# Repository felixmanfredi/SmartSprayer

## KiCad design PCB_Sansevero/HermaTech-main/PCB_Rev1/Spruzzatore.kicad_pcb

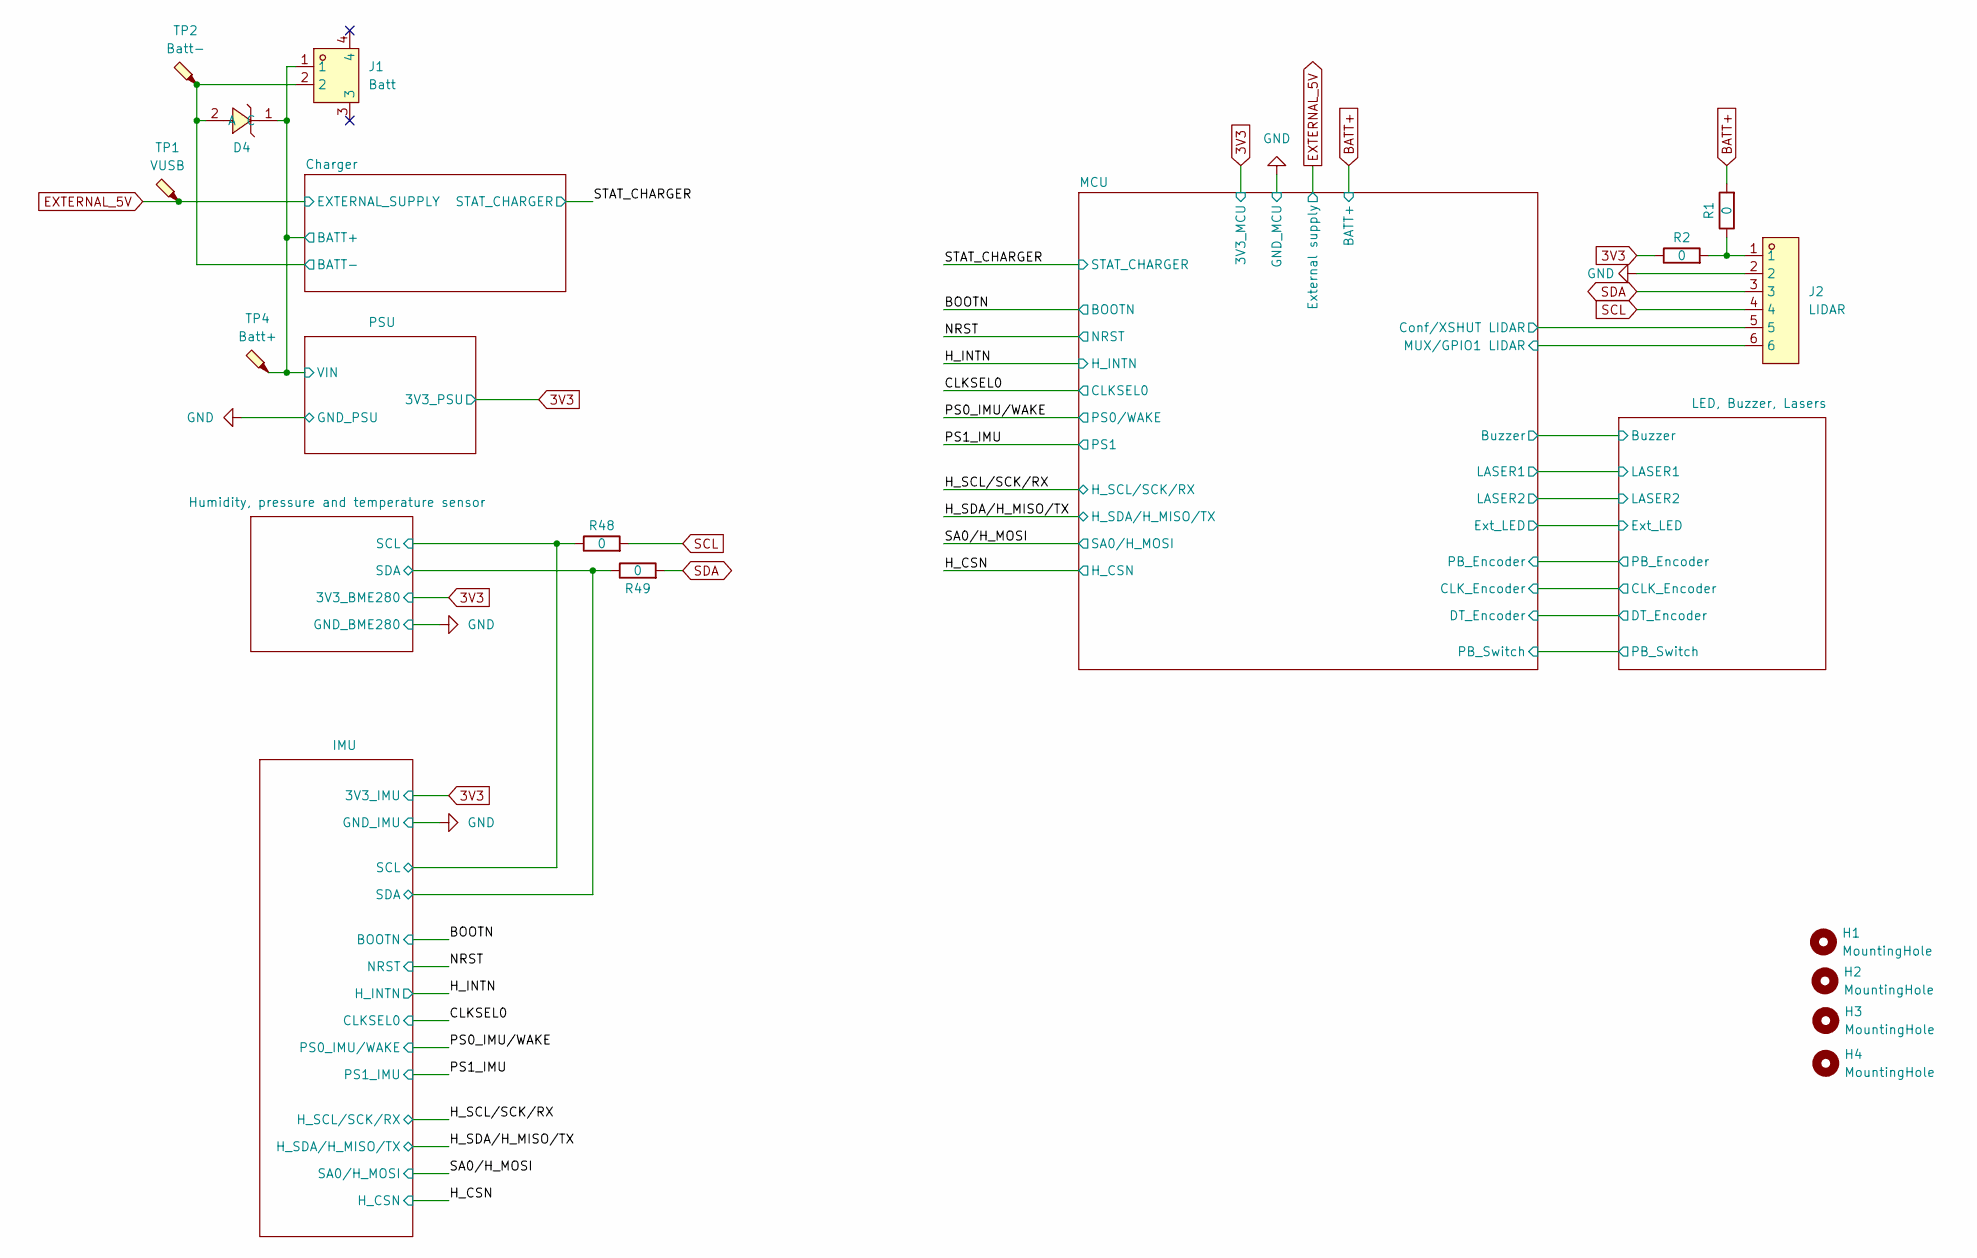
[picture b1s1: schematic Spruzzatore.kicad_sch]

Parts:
D4: SLESD4V5S; SOD-323_L1.7-W1.3-LS2.6-RD-1; LCSC Part C5155454
H1, H2, H3, H4: MountingHole; MountingHole_3.2mm_M3_DIN965_Pad
J1: Batt; CONN-SMD_P2.00_S2B-PH-SM4-TB-LF-SN; LCSC Part C295747
J2: LIDAR; CONN-TH_6P-P1.25_BX-MX1.25-6PZZ; LCSC Part C22388452
R1, R2, R48, R49: 0; R0603; LCSC Part C21189
TP1: VUSB; TestPoint_Pad_D1.0mm
TP2: Batt-; TestPoint_Pad_1.0x1.0mm
TP4: Batt+; TestPoint_Pad_D1.0mm

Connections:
3V3: R2.1; also elsewhere on the board
/Charger/BATT-: D4.2 (A), J1.2, TP2.1; also elsewhere on the board
/Charger/B_CHG_+: D4.1 (C), J1.1, TP4.1; also elsewhere on the board
/Humidity, pressure and temperature sensor/SCL: R48.1; also elsewhere on the board
/Humidity, pressure and temperature sensor/SDA: R49.1; also elsewhere on the board
/MCU/Conf/XSHUT LIDAR: J2.5; also elsewhere on the board
/MCU/MUX/GPIO1 LIDAR: J2.6; also elsewhere on the board
BATT+: R1.2; also elsewhere on the board
EXTERNAL_5V: TP1.1; also elsewhere on the board
GND: J2.2; also elsewhere on the board
unnamed: J2.1, R1.1, R2.2
SCL: J2.4, R48.2; also elsewhere on the board
SDA: J2.3, R49.2; also elsewhere on the board

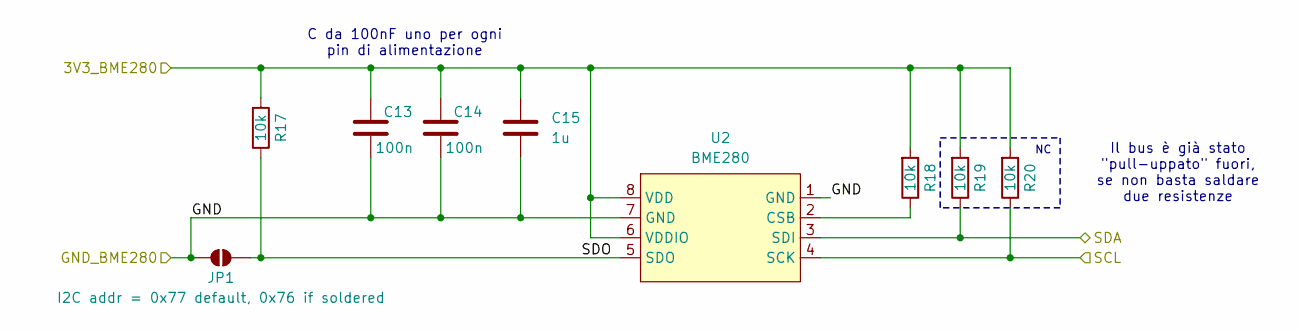
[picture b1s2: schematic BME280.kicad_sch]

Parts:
C13, C14: 100n; C0603; LCSC Part C14663
C15: 1u; C0603; LCSC Part C15849
JP1: I2C addr = 0x77 default, 0x76 if soldered; SolderJumper-2_P1.3mm_Open_RoundedPad1.0x1.5mm
R17, R18, R19, R20: 10k; R0603; LCSC Part C25804
U2: BME280; LGA-8_BME280_BL; LCSC Part C92489

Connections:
3V3: C13.1, C14.1, C15.1, R17.2, R18.2, R19.2, R20.2, U2.6 (VDDIO), U2.8 (VDD); also elsewhere on the board
/Humidity, pressure and temperature sensor/SCL: R20.1, U2.4 (SCK); also elsewhere on the board
/Humidity, pressure and temperature sensor/SDA: R19.1, U2.3 (SDI); also elsewhere on the board
/Humidity, pressure and temperature sensor/SDO: JP1.1 (A), R17.1, U2.5 (SDO)
GND: C13.2, C14.2, C15.2, JP1.2 (B), U2.1 (GND), U2.7 (GND); also elsewhere on the board
unnamed: R18.1, U2.2 (CSB)

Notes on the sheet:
C da 100nF uno per ogni pin di alimentazione
Il bus è già stato "pull-uppato" fuori, se non basta saldare due resistenze

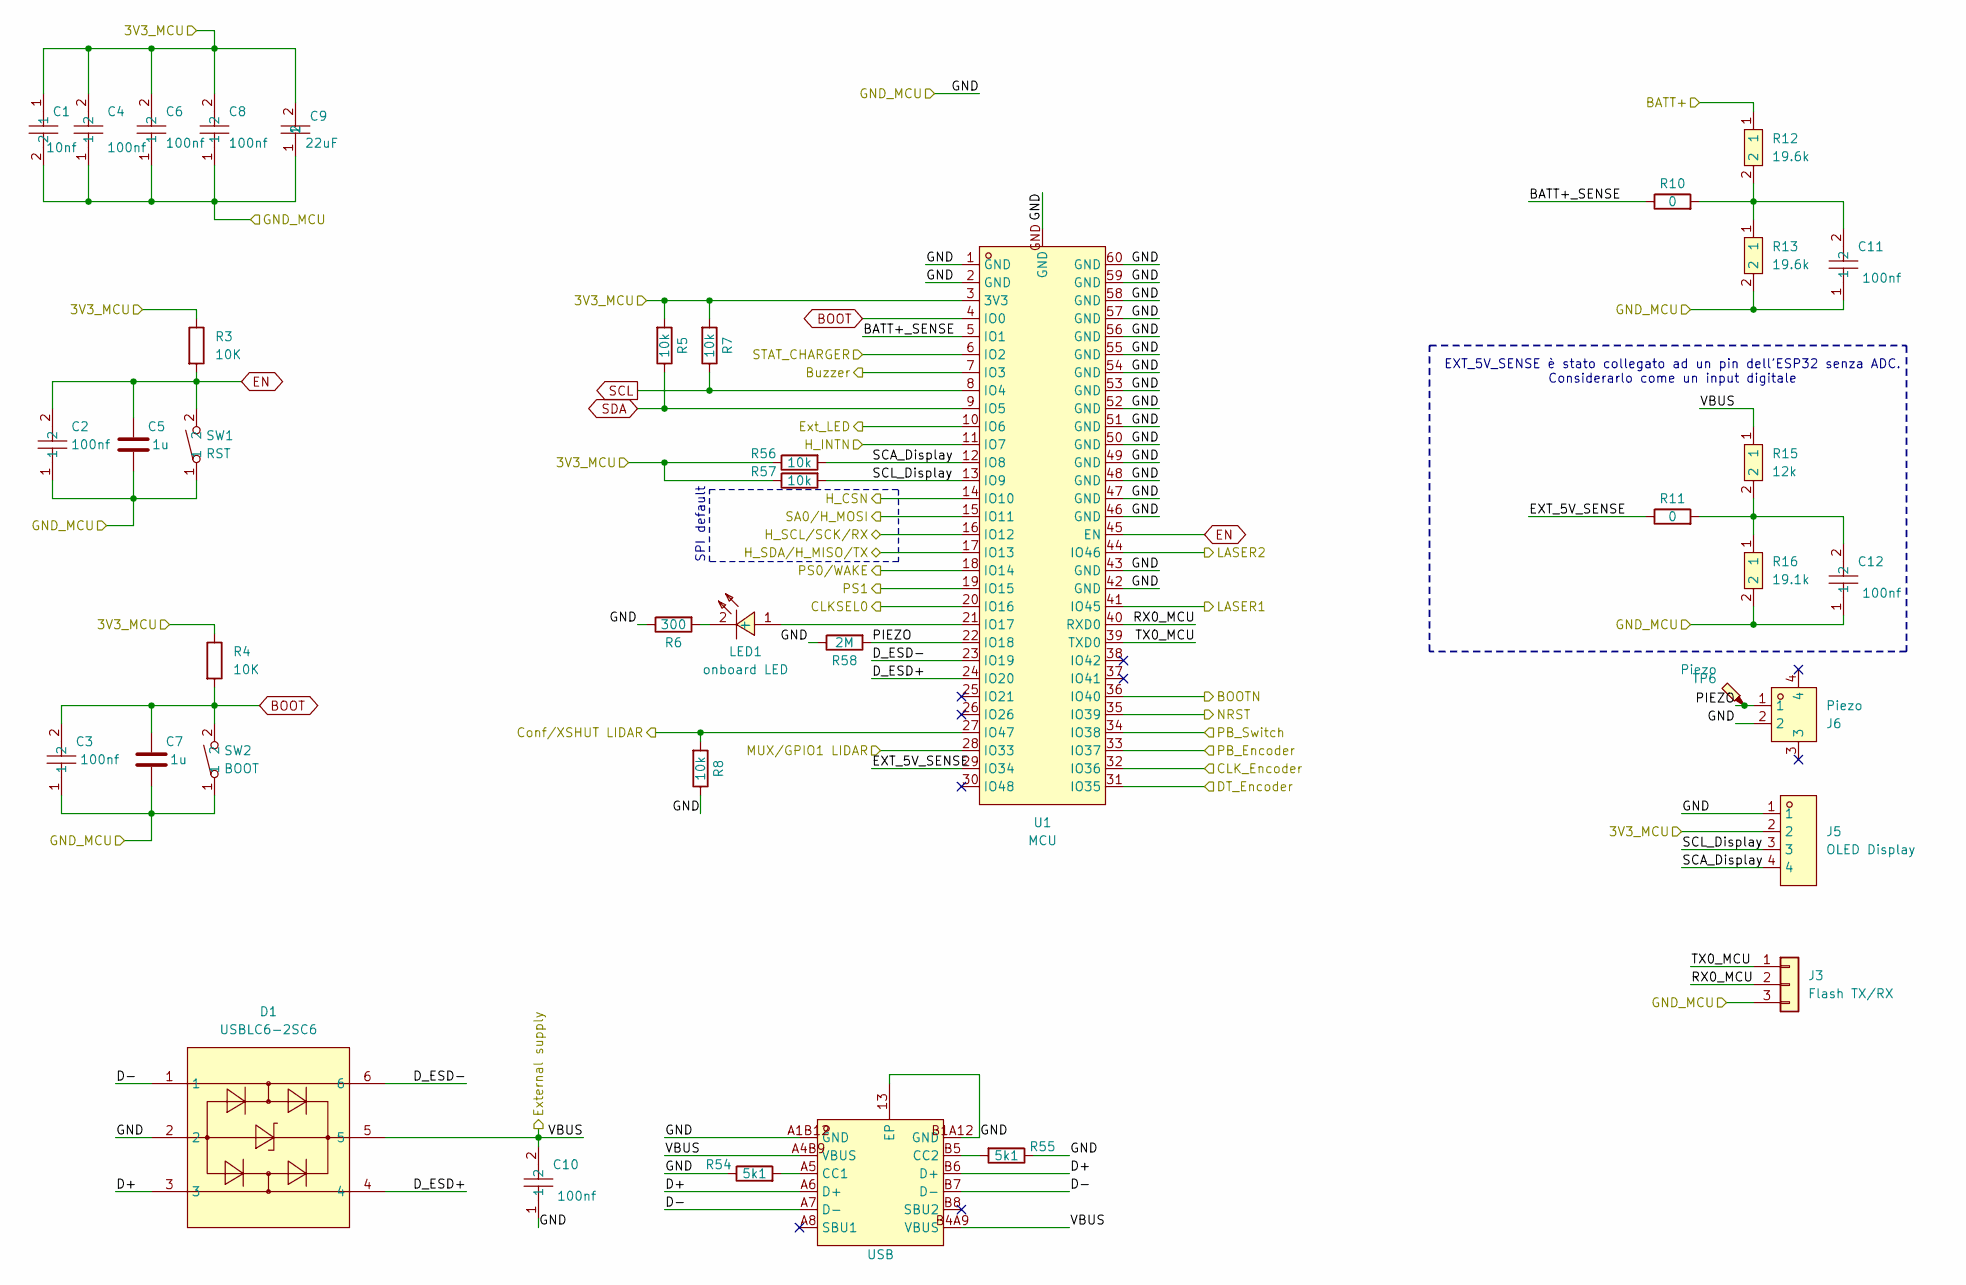
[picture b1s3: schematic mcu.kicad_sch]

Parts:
C1: 10nf; C0603; LCSC Part C57112
C2, C3, C4, C6, C8, C10, C11, C12: 100nf; C0603; LCSC Part C14663
C5, C7: 1u; C0603; LCSC part C15849
C9: 22uF; C1206; LCSC Part C12891
D1: USBLC6-2SC6; SOT-23-6_L2.9-W1.6-P0.95-LS2.8-BL; LCSC Part C2687116
J3: Flash TX/RX; JST_GH_SM03B-GHS-TB_1x03-1MP_P1.25mm_Horizontal
J5: OLED Display; CONN-TH_4P-P1.25_WAFER-MX1.25-4PZZ; LCSC Part C22390409
J6: Piezo; CONN-SMD_2P-P1.25_XUNPU_WAFER-MX1.25-2PWB; LCSC Part C3029359
LED1: onboard LED; LED0805-R-RD; LCSC Part C84256
R3, R4: 10K; R0603; LCSC Part C25804
R5, R7, R56, R57: 10k; R0603; LCSC Part C25804
R6: 300; R0603; LCSC Part C23025
R8: 10k; R0603
R10, R11: 0; R0603; LCSC Part C21189
R12, R13: 19.6k; R0603; LCSC Part C861185
R15: 12k; R0603; LCSC Part C861185
R16: 19.1k; R0603; LCSC Part C861097
R54, R55: 5k1; R0603; LCSC C23186
R58: 2M; R0603; LCSC Part C23025
SW1: RST; SW-SMD_L3.9-W2.9-P4.15-LS5.0; LCSC Part C493285
SW2: BOOT; SW-SMD_L3.9-W2.9-P4.15-LS5.0; LCSC Part C493285
TP6: Piezo; TestPoint_Pad_D1.0mm
U1: MCU; BULETM-SMD_ESP32-S3-MINI-1-N8; LCSC Part C3013941
USB1: USB; USB-C-SMD_TYPE-C-16P-1; LCSC Part C2982555

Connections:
3V3: C1.1, C4.2, C6.2, C8.2, C9.2, J5.2, R3.1, R4.1, R5.2, R7.2, R56.1, R57.1, U1.3 (3V3); also elsewhere on the board
/BOOTN: U1.36 (IO40); also elsewhere on the board
/CLKSEL0: U1.20 (IO16); also elsewhere on the board
/H_CSN: U1.14 (IO10); also elsewhere on the board
/H_INTN: U1.11 (IO7); also elsewhere on the board
/H_SCL/SCK/RX: U1.16 (IO12); also elsewhere on the board
/H_SDA/H_MISO/TX: U1.17 (IO13); also elsewhere on the board
/LED, Buzzer, Lasers/Buzzer: U1.7 (IO3); also elsewhere on the board
/LED, Buzzer, Lasers/CLK_Encoder: U1.32 (IO36); also elsewhere on the board
/LED, Buzzer, Lasers/DT_Encoder: U1.31 (IO35); also elsewhere on the board
/LED, Buzzer, Lasers/Ext_LED: U1.10 (IO6); also elsewhere on the board
/LED, Buzzer, Lasers/LASER1: U1.41 (IO45); also elsewhere on the board
/LED, Buzzer, Lasers/LASER2: U1.44 (IO46); also elsewhere on the board
/LED, Buzzer, Lasers/PB_Encoder: U1.33 (IO37); also elsewhere on the board
/LED, Buzzer, Lasers/PB_Switch: U1.34 (IO38); also elsewhere on the board
/MCU/BATT+_SENSE: R10.1, U1.5 (IO1)
/MCU/Conf/XSHUT LIDAR: R8.2, U1.27 (IO47); also elsewhere on the board
/MCU/D+: D1.3, USB1.A6 (D+), USB1.B6 (D+)
/MCU/D-: D1.1, USB1.A7 (D-), USB1.B7 (D-)
/MCU/D_ESD+: D1.4, U1.24 (IO20)
/MCU/D_ESD-: D1.6, U1.23 (IO19)
/MCU/EXT_5V_SENSE: R11.1, U1.29 (IO34)
/MCU/MUX/GPIO1 LIDAR: U1.28 (IO33); also elsewhere on the board
/MCU/PIEZO: J6.1, R58.2, TP6.1, U1.22 (IO18)
/MCU/RX0_MCU: J3.2, U1.40 (RXD0)
/MCU/SCA_Display: J5.4, R56.2, U1.12 (IO8)
/MCU/SCL_Display: J5.3, R57.2, U1.13 (IO9)
/MCU/TX0_MCU: J3.1, U1.39 (TXD0)
/NRST: U1.35 (IO39); also elsewhere on the board
/PS0_IMU/WAKE: U1.18 (IO14); also elsewhere on the board
/PS1_IMU: U1.19 (IO15); also elsewhere on the board
/SA0/H_MOSI: U1.15 (IO11); also elsewhere on the board
/STAT_CHARGER: U1.6 (IO2); also elsewhere on the board
BATT+: R12.1; also elsewhere on the board
BOOT: C3.2, C7.1, R4.2, SW2.2, U1.4 (IO0)
EN: C2.2, C5.1, R3.2, SW1.2, U1.45 (EN)
EXTERNAL_5V: C10.2, D1.5, R15.1, USB1.A4B9 (VBUS), USB1.B4A9 (VBUS); also elsewhere on the board
GND: C1.2, C2.1, C3.1, C4.1, C5.2, C6.1, C7.2, C8.1, C9.1, C10.1, C11.1, C12.1, D1.2, J3.3, J5.1, J6.2, R6.1, R8.1, R13.2, R16.2, R54.1, R55.1, R58.1, SW1.1, SW2.1, U1.1 (GND), U1.2 (GND), U1.42 (GND), U1.43 (GND), U1.46 (GND), U1.47 (GND), U1.48 (GND), U1.49 (GND), U1.50 (GND), U1.51 (GND), U1.52 (GND), U1.53 (GND), U1.54 (GND), U1.55 (GND), U1.56 (GND), U1.57 (GND), U1.58 (GND), U1.59 (GND), U1.60 (GND), U1.GND, USB1.13 (EP), USB1.A1B12 (GND), USB1.B1A12 (GND); also elsewhere on the board
unnamed: C11.2, R10.2, R12.2, R13.1
unnamed: C12.2, R11.2, R15.2, R16.1
unnamed: LED1.1 (+), U1.21 (IO17)
unnamed: LED1.2 (-), R6.2
unnamed: R54.2, USB1.A5 (CC1)
unnamed: R55.2, USB1.B5 (CC2)
SCL: R7.1, U1.8 (IO4); also elsewhere on the board
SDA: R5.1, U1.9 (IO5); also elsewhere on the board

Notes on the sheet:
SPI default
EXT_5V_SENSE è stato collegato ad un pin dell'ESP32 senza ADC. Considerarlo come un input digitale

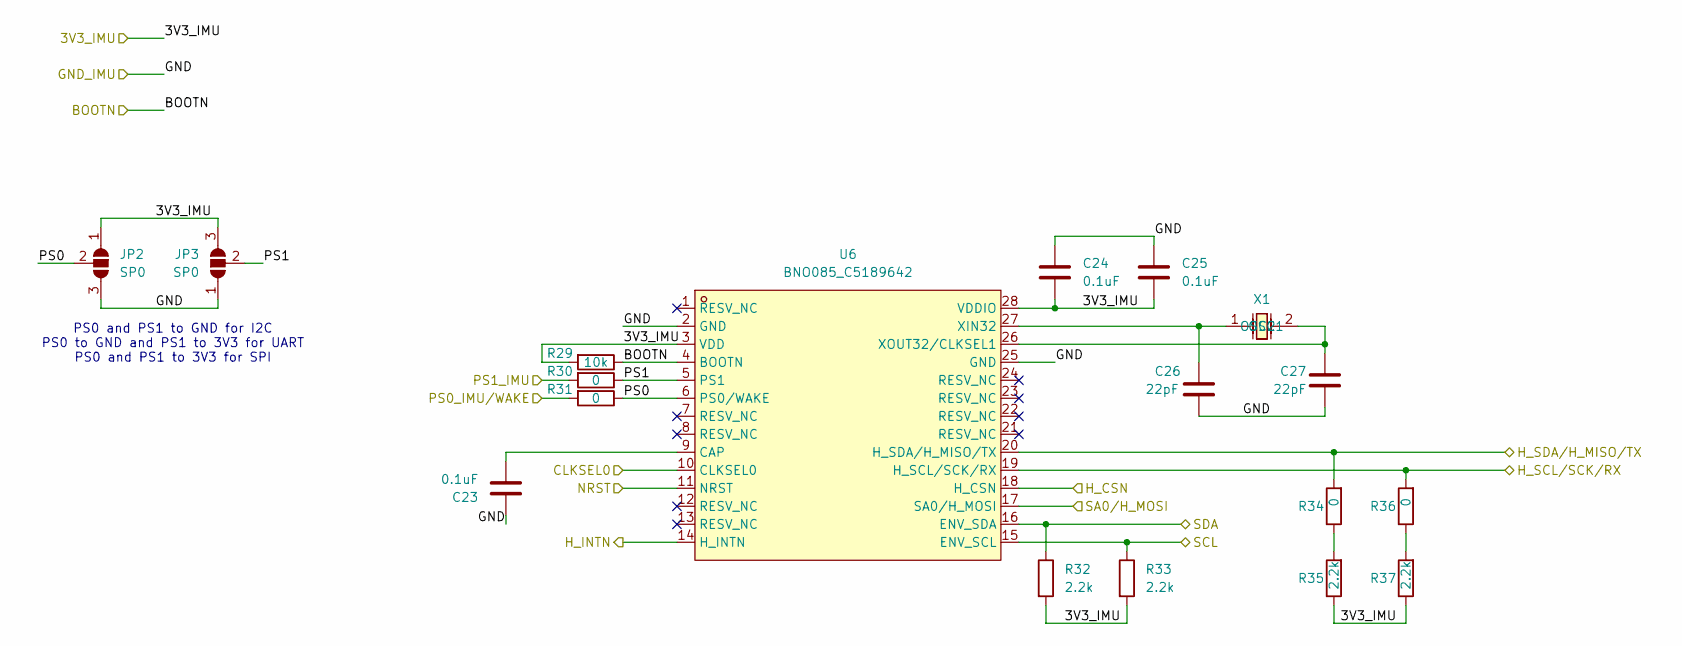
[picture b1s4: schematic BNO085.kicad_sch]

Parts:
C23, C24, C25: 0.1uF; C0603
C26, C27: 22pF; C0603
JP2, JP3: SP0; SolderJumper-3_P1.3mm_Open_RoundedPad1.0x1.5mm
R29: 10k; R0603; LCSC Part C21189
R30, R31: 0; R0603; LCSC Part C21189
R32, R33, R35, R37: 2.2k; R0603
R34, R36: 0; R0603
U6: BNO085_C5189642; LGA-28_L5.2-W3.8-P0.50-BL; LCSC Part C5189642
X1: ABS06-32.768KHZ-T; OSC-SMD_L2.0-W1.2; LCSC Part C276423

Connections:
3V3: C24.2, C25.2, JP2.1 (A), JP3.3 (B), R29.2, R32.2, R33.2, R35.1, R37.1, U6.3 (VDD), U6.28 (VDDIO); also elsewhere on the board
/BOOTN: R29.1, U6.4 (BOOTN); also elsewhere on the board
/CLKSEL0: U6.10 (CLKSEL0); also elsewhere on the board
/H_CSN: U6.18 (H_CSN); also elsewhere on the board
/H_INTN: U6.14 (H_INTN); also elsewhere on the board
/H_SCL/SCK/RX: R36.2, U6.19 (H_SCL/SCK/RX); also elsewhere on the board
/H_SDA/H_MISO/TX: R34.2, U6.20 (H_SDA/H_MISO/TX); also elsewhere on the board
/Humidity, pressure and temperature sensor/SCL: R33.1, U6.15 (ENV_SCL); also elsewhere on the board
/Humidity, pressure and temperature sensor/SDA: R32.1, U6.16 (ENV_SDA); also elsewhere on the board
/IMU/PS0: JP2.2 (C), R31.1, U6.6 (PS0/WAKE)
/IMU/PS1: JP3.2 (C), R30.1, U6.5 (PS1)
/NRST: U6.11 (NRST); also elsewhere on the board
/PS0_IMU/WAKE: R31.2; also elsewhere on the board
/PS1_IMU: R30.2; also elsewhere on the board
/SA0/H_MOSI: U6.17 (SA0/H_MOSI); also elsewhere on the board
GND: C23.1, C24.1, C25.1, C26.1, C27.1, JP2.3 (B), JP3.1 (A), U6.2 (GND), U6.25 (GND); also elsewhere on the board
unnamed: R34.1, R35.2
unnamed: R36.1, R37.2
unnamed: C23.2, U6.9 (CAP)
unnamed: C26.2, U6.27 (XIN32), X1.1 (OSC1)
unnamed: C27.2, U6.26 (XOUT32/CLKSEL1), X1.2 (OSC2)

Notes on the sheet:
PS0 and PS1 to GND for I2C PS0 to GND and PS1 to 3V3 for UART PS0 and PS1 to 3V3 for SPI

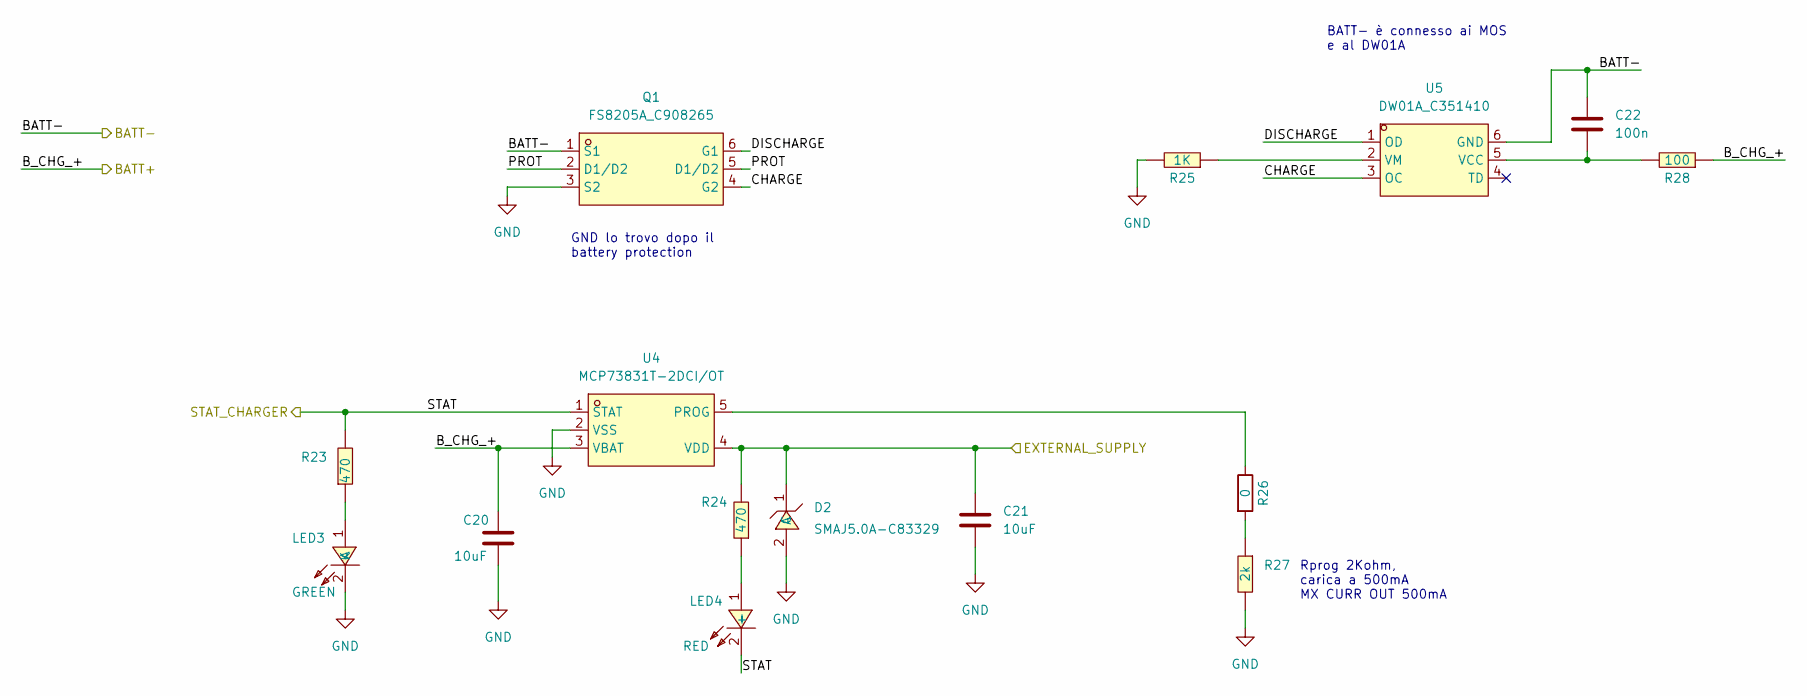
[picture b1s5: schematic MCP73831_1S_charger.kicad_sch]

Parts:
C20, C21: 10uF; C0603
C22: 100n; C0603
D2: SMAJ5.0A-C83329; SMA_L4.3-W2.6-LS5.2-RD; LCSC Part C83329
LED3: GREEN; LED0805-R-RD; LCSC Part C2297
LED4: RED; LED0805-R-RD; LCSC Part C84256
Q1: FS8205A_C908265; SOT-23-6_L2.9-W1.6-P0.95-LS2.8-BR; LCSC Part C908265
R23, R24: 470; R0603
R25: 1K; R0603
R26: 0; R0603; LCSC Part C21189
R27: 2k; R0603
R28: 100; R0603
U4: MCP73831T-2DCI/OT; SOT-23-5_L2.9-W1.6-P0.95-LS2.8-BL; LCSC Part C625597
U5: DW01A_C351410; SOT-23-6_L2.9-W1.6-P0.95-LS2.8-BL; LCSC Part C351410

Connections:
/Charger/BATT-: C22.1, Q1.1 (S1), U5.6 (GND); also elsewhere on the board
/Charger/B_CHG_+: C20.1, R28.1, U4.3 (VBAT); also elsewhere on the board
/Charger/CHARGE: Q1.4 (G2), U5.3 (OC)
/Charger/DISCHARGE: Q1.6 (G1), U5.1 (OD)
/Charger/PROT: Q1.2 (D1/D2), Q1.5 (D1/D2)
/STAT_CHARGER: LED4.2 (-), R23.2, U4.1 (STAT); also elsewhere on the board
EXTERNAL_5V: C21.1, D2.1 (C), R24.2, U4.4 (VDD); also elsewhere on the board
GND: C20.2, C21.2, D2.2 (A), LED3.2 (K), Q1.3 (S2), R25.2, R27.2, U4.2 (VSS); also elsewhere on the board
unnamed: LED3.1 (A), R23.1
unnamed: LED4.1 (+), R24.1
unnamed: R26.2, R27.1
unnamed: R26.1, U4.5 (PROG)
unnamed: C22.2, R28.2, U5.5 (VCC)
unnamed: R25.1, U5.2 (VM)

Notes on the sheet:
Rprog 2Kohm, carica a 500mA MX CURR OUT 500mA
GND lo trovo dopo il battery protection
BATT- è connesso ai MOS e al DW01A

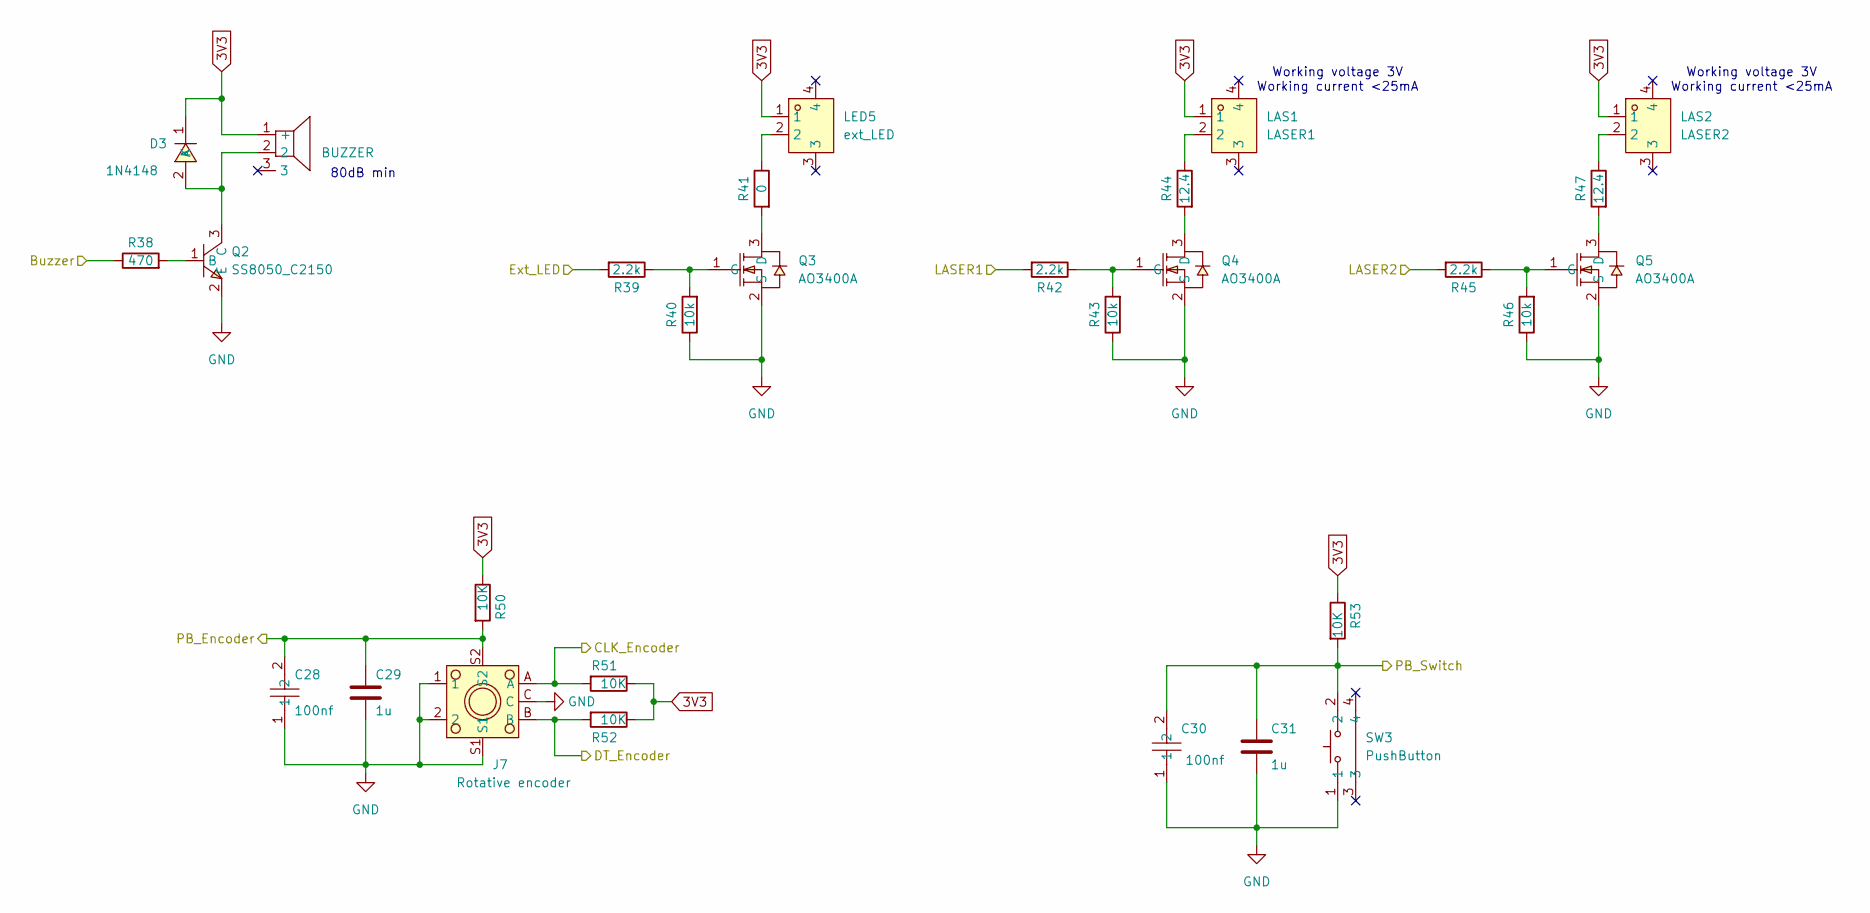
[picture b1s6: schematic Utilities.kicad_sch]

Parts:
BUZZER1: BUZZER; BUZ-SMD_FST-5025; LCSC Part C391030
C28, C30: 100nf; C0603; LCSC Part C14663
C29, C31: 1u; C0603; LCSC part C15849
D3: 1N4148; SOD-123F_L2.7-W1.6-LS3.8-RD; LCSC Part C81598
J7: Rotative encoder; SW-TH_CTR_ED08905M-FE15C7.0-C10-2053; LCSC Part C18213469
LAS1: LASER1; CONN-SMD_2P-P1.25_XUNPU_WAFER-MX1.25-2PWB; LCSC Part C3029359
LAS2: LASER2; CONN-SMD_2P-P1.25_XUNPU_WAFER-MX1.25-2PWB; LCSC Part C3029359
LED5: ext_LED; CONN-SMD_2P-P1.25_XUNPU_WAFER-MX1.25-2PWB; LCSC Part C3029359
Q2: SS8050_C2150; SOT-23-3_L2.9-W1.3-P1.90-LS2.4-BR; LCSC Part C2150
Q3, Q4, Q5: AO3400A; SOT-23-3_L2.9-W1.3-P1.90-LS2.4-BR; LCSC Part C20917
R38: 470; R0603; LCSC C441919
R39, R42, R45: 2.2k; R0603; LCSC Part C4190
R40, R43, R46: 10k; R0603; LCSC Part C25804
R41: 0; R0603; LCSC Part C17888
R44, R47: 12.4; R0603; LCSC Part C22786
R50, R51, R52, R53: 10K; R0603; LCSC Part C25804
SW3: PushButton; SW-TH_SKHHNJA010; LCSC Part C470264

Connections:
3V3: BUZZER1.1 (+), D3.1 (K), LAS1.1, LAS2.1, LED5.1, R50.1, R51.1, R52.1, R53.1; also elsewhere on the board
/LED, Buzzer, Lasers/Buzzer: R38.1; also elsewhere on the board
/LED, Buzzer, Lasers/CLK_Encoder: J7.A, R51.2; also elsewhere on the board
/LED, Buzzer, Lasers/DT_Encoder: J7.B, R52.2; also elsewhere on the board
/LED, Buzzer, Lasers/Ext_LED: R39.2; also elsewhere on the board
/LED, Buzzer, Lasers/LASER1: R42.2; also elsewhere on the board
/LED, Buzzer, Lasers/LASER2: R45.2; also elsewhere on the board
/LED, Buzzer, Lasers/PB_Encoder: C28.2, C29.1, J7.S2, R50.2; also elsewhere on the board
/LED, Buzzer, Lasers/PB_Switch: C30.2, C31.1, R53.2, SW3.2; also elsewhere on the board
GND: C28.1, C29.2, C30.1, C31.2, J7.1, J7.2, J7.C, J7.S1, Q2.2 (E), Q3.2 (S), Q4.2 (S), Q5.2 (S), R40.1, R43.1, R46.1, SW3.1; also elsewhere on the board
unnamed: BUZZER1.2, D3.2 (A), Q2.3 (C)
unnamed: LAS1.2, R44.1
unnamed: LAS2.2, R47.1
unnamed: LED5.2, R41.1
unnamed: Q2.1 (B), R38.2
unnamed: Q3.3 (D), R41.2
unnamed: Q3.1 (G), R39.1, R40.2
unnamed: Q4.3 (D), R44.2
unnamed: Q4.1 (G), R42.1, R43.2
unnamed: Q5.3 (D), R47.2
unnamed: Q5.1 (G), R45.1, R46.2

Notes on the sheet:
Working voltage 3V Working current <25mA
80dB min

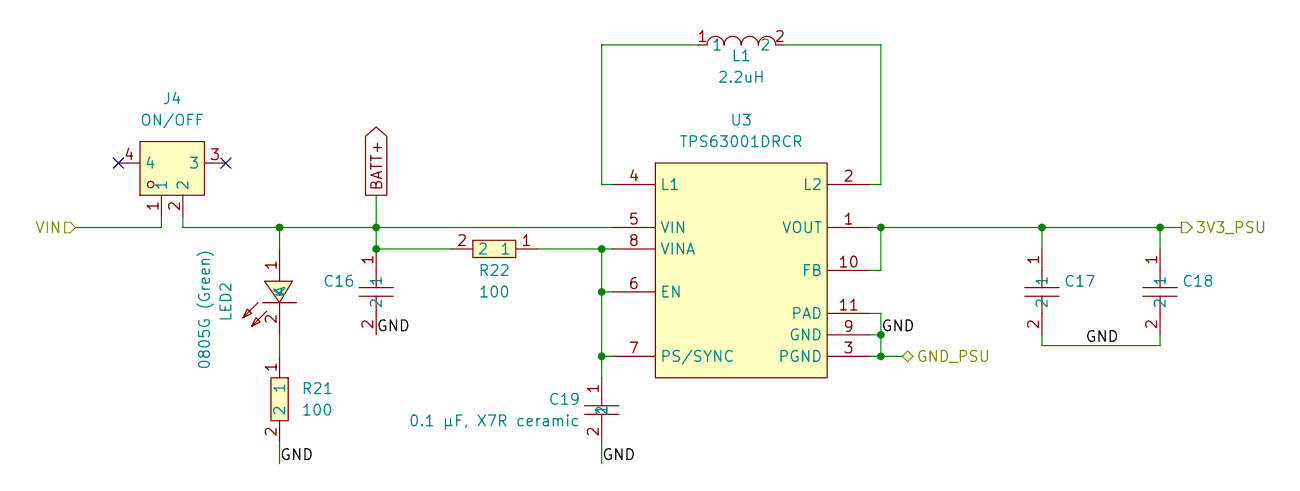
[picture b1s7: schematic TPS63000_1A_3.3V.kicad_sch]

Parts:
C16, C17, C18: CL10B106MQ8NRNC; C0603; LCSC Part C3039698
C19: CL10B104KA8NNNC; C0603; LCSC Part C1590
J4: ON/OFF; CONN-SMD_2P-P1.25_XUNPU_WAFER-MX1.25-2PWB; LCSC Part C3029359
L1: LQH3NPN2R2MMEL; IND-SMD_L3.0-W3.0_LQH3NPN2R2NG0L; LCSC Part C668451
LED2: 0805G (Green); LED0805-R-RD; LCSC Part C2297
R21, R22: 100; R0603; LCSC Part C22775
U3: TPS63001DRCR; VSON-10_L3.0-W3.0-P0.50-TL-EP_TPS62410DRCR; LCSC Part C28060

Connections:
3V3: C17.1, C18.1, U3.1 (VOUT), U3.10 (FB); also elsewhere on the board
/Charger/B_CHG_+: J4.1; also elsewhere on the board
BATT+: C16.1, J4.2, LED2.1 (A), R22.2, U3.5 (VIN); also elsewhere on the board
GND: C16.2, C17.2, C18.2, C19.2, R21.2, U3.3 (PGND), U3.9 (GND), U3.11 (PAD); also elsewhere on the board
unnamed: LED2.2 (K), R21.1
unnamed: C19.1, R22.1, U3.6 (EN), U3.7 (PS/SYNC), U3.8 (VINA)
unnamed: L1.1, U3.4 (L1)
unnamed: L1.2, U3.2 (L2)

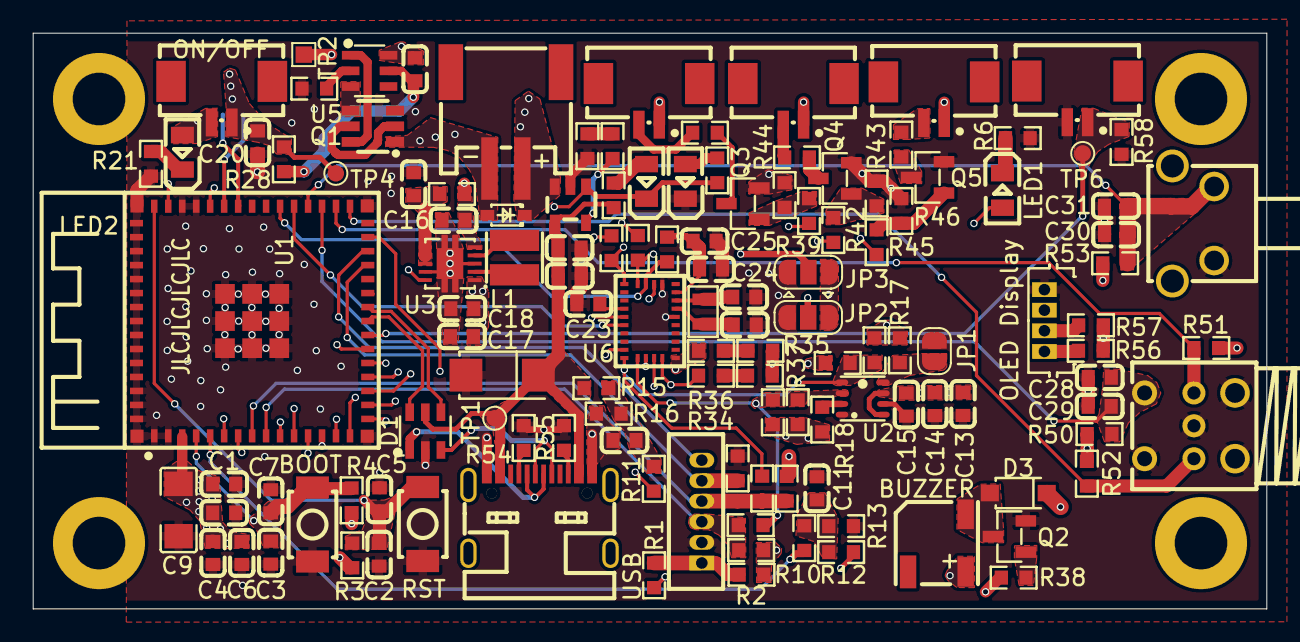
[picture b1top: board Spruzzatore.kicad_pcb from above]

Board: 4 copper layers, 75.0 x 35.0 mm, 134 parts (1 on the bottom side), 84 nets.

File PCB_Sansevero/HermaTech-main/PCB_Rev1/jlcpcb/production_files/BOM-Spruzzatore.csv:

Comment,Designator,Footprint,LCSC,Quantity
22uF,C9,C1206,C12891,1
100nf,"C10,C11,C12,C13,C14,C2,C22,C23,C24,C25,C28,C3,C30,C4,C6,C8",C0603,C14663,16
1u,"C15,C29,C31,C5,C7",C0603,C15849,5
CL10B104KA8NNNC,C19,C0603,C1590,1
22pF,"C26,C27",C0603,C1653,2
Rotative encoder,J7,SW-TH_CTR_ED08905M-FE15C7.0-C10-2053,C18213469,1
10uF,"C20,C21",C0603,C19702,2
AO3400A,"Q3,Q4,Q5",SOT-23-3_L2.9-W1.3-P1.90-LS2.4-BR,C20917,3
0,"R1,R10,R11,R26,R30,R31,R41",R0603,C21189,7
1K,R25,R0603,C21190,1
SS8050_C2150,Q2,SOT-23-3_L2.9-W1.3-P1.90-LS2.4-BR,C2150,1
LIDAR,J2,CONN-TH_6P-P1.25_BX-MX1.25-6PZZ,C22388452,1
OLED Display,J5,CONN-TH_4P-P1.25_WAFER-MX1.25-4PZZ,C22390409,1
100,"R21,R22,R28",R0603,C22775,3
12.4,"R44,R47",R0603,C22786,2
12k,R15,R0603,C22790,1
19.1k,R16,R0603,C22897,1
0805G (Green),"LED2,LED3",LED0805-R-RD,C2297,2
2k,R27,R0603,C22975,1
2M,R58,R0603,C22976,1
300,R6,R0603,C23025,1
470,"R23,R24,R38",R0603,C23179,3
5k1,"R54,R55",R0603,C23186,2
10k,"R17,R18,R29,R3,R4,R40,R43,R46,R50,R51,R52,R53",R0603,C25804,12
USBLC6-2SC6,D1,SOT-23-6_L2.9-W1.6-P0.95-LS2.8-BL,C2687116,1
ABS06-32.768KHZ-T,X1,OSC-SMD_L2.0-W1.2,C276423,1
TPS63001DRCR,U3,VSON-10_L3.0-W3.0-P0.50-TL-EP_TPS62410DRCR,C28060,1
Batt,J1,CONN-SMD_P2.00_S2B-PH-SM4-TB-LF-SN,C295747,1
USB,USB1,USB-C-SMD_TYPE-C-16P-1,C2982555,1
MCU,U1,BULETM-SMD_ESP32-S3-MINI-1-N8,C3013941,1
ON/OFF,"J4,J6,LAS1,LAS2,LED5",CONN-SMD_2P-P1.25_XUNPU_WAFER-MX1.25-2PWB,C3029359,5
CL10B106MQ8NRNC,"C16,C17,C18",C0603,C3039698,3
DW01A_C351410,U5,SOT-23-6_L2.9-W1.6-P0.95-LS2.8-BL,C351410,1
BUZZER,BUZZER1,BUZ-SMD_FST-5025,C391030,1
2.2k,"R32,R33,R35,R37,R39,R42,R45",R0603,C4190,7
PushButton,SW3,SW-TH_SKHHNJA010,C470264,1
RST,"SW1,SW2",SW-SMD_L3.9-W2.9-P4.15-LS5.0,C493285,2
SLESD4V5S,D4,SOD-323_L1.7-W1.3-LS2.6-RD-1,C5155454,1
BNO085_C5189642,U6,LGA-28_L5.2-W3.8-P0.50-BL,C5189642,1
10nf,C1,C0603,C57112,1
MCP73831T-2DCI/OT,U4,SOT-23-5_L2.9-W1.6-P0.95-LS2.8-BL,C625597,1
LQH3NPN2R2MMEL,L1,IND-SMD_L3.0-W3.0_LQH3NPN2R2NG0L,C668451,1
1N4148,D3,SOD-123F_L2.7-W1.6-LS3.8-RD,C81598,1
SMAJ5.0A-C83329,D2,SMA_L4.3-W2.6-LS5.2-RD,C83329,1
onboard LED,"LED1,LED4",LED0805-R-RD,C84256,2
124k,R14,R0603,C861097,1
19.6k,"R12,R13",R0603,C861185,2
FS8205A_C908265,Q1,SOT-23-6_L2.9-W1.6-P0.95-LS2.8-BR,C908265,1
BME280,U2,LGA-8_BME280_BL,C92489,1

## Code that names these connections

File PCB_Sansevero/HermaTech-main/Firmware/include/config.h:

#define EXT_LED 6
#define LASER1 45
#define LASER2 46
#define BUZZER 3
#define BATT_SENSE 1
#define EXT_5V_SENSE 34
#define STAT_CHARGER 2
#define SCL 4
#define SCA 5
#define SCL_DISPLAY 9
#define SCA_DISPLAY 8
#define H_CSN 10
#define H_MOSI 11
#define H_SCL 12
#define H_SDA 13
#define PS0 14
#define PS1 15
#define CLKSEL0 16
#define ONBOARDLED 17
#define XSHUT 47
#define GPIO1 33
#define BOOTN 36
#define NRST 39
#define PB_SWITCH 38
#define PB_ENCODER 37
#define CLK_ENCODER 36
#define DT_ENCODER 35  


/**
 * @brief The baud rate for serial communication.
 *
 * This constant sets the data transfer rate for the serial port,
 */
const unsigned long SERIAL_BAUD = 115200;

/**
 * @brief The delay in milliseconds after serial communication is initialized.
 *
 * This delay provides a brief pause after setting up the serial port,
 * allowing the serial connection to stabilize before any data transmission begins.
 * It can be useful to ensure that the connected device is ready to receive commands or data.
 */
const unsigned long DELAY_AFTER_SERIAL_INITIALIZED = 100;

/**
 * @brief The name of the BLE server/device.
 *
 * This name is displayed when scanning for BLE devices.
 */
const char *BLE_SERVER_NAME = "HermaTech";


/**
 * @brief A GATT characteristic that can publish sensor data.
 */
const char *TELEMETRY_UUID = "38938a29-7798-4dd6-bca2-c8fc70f65bfc";


/**
 * @brief A GATT characteristic that receive commands
 */
const char *COMMANDS_UUID = "f7a40c1c-e012-4c18-b838-51de426a868c";


//////////////////////////////////////////////////////////////



/**
 * @brief A GATT characteristic that can publish geomagnetic data.
 */
const char *MAGNETOMETER_UUID = "5d08a535-513b-47ce-8b28-7178dcfb69aa";

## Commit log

2025-11-18 first commit
    La Rev_0 è stata realizzata fisicamente
2025-11-19 Add files via upload
    add Firmware
2025-11-28 BME280 escluso
2025-12-10 modifica gestione piezo e pagine del display
